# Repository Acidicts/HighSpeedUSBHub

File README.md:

# HighSpeedUSBHub

I looked at an old USB 2.0 hub I made and though what if I could make a faster one? So I did(whether it works or not is another story). This started right after I discovered the [texas instruments](https://www.ti.com/) site via the guide for making a flight controller by @notaroomba.

This is a USB 3.1 hub which uses a usb 3.1 gen 2 upstream port to 4 usb 3.0 downstream ports via a [`TUSB8041`](https://www.ti.com/product/TUSB8041). Each USB stack (I used x2 stacked usb 3.0 ports as they were more compact, and they reminded me of the raspberry pi 4) is powered by a [`TPS2051B`](https://www.ti.com/product/TPS2051B) which is a power switch that has a power limit of around 1A per controller as I recall.

### Features
- 4 USB-A 3.0 downstream ports
- 1 USB-C 3.1 gen 2 upstream port
- Powered by the USB-C port (5V 3A)
- Each downstream port is limited to 1A of current and with equal load across each port, 0.5A per port.
- CRYSTAL 24MHz clock for the TUSB8041

<div class="inline-flex">

</div>

### Case
Fusion 360 Link [here](https://a360.co/4czpJdL)
There are two parts of the case:
- The [Lid](case/Lid.stp)
- The [Base](case/Base.stp)
The lid has notches which slot into the base to hold it on using the power of friendship and friction.

### Getting Started
So ummm, how do I put this...

_*YOU PLUG IT IN*_

### Firmware
Sooo you won't believe this but it is just a usb hub, it is plug and play

### BOMs
- [BOM](BOM.csv)
- [PCB BOM](PCB_BOM.csv)

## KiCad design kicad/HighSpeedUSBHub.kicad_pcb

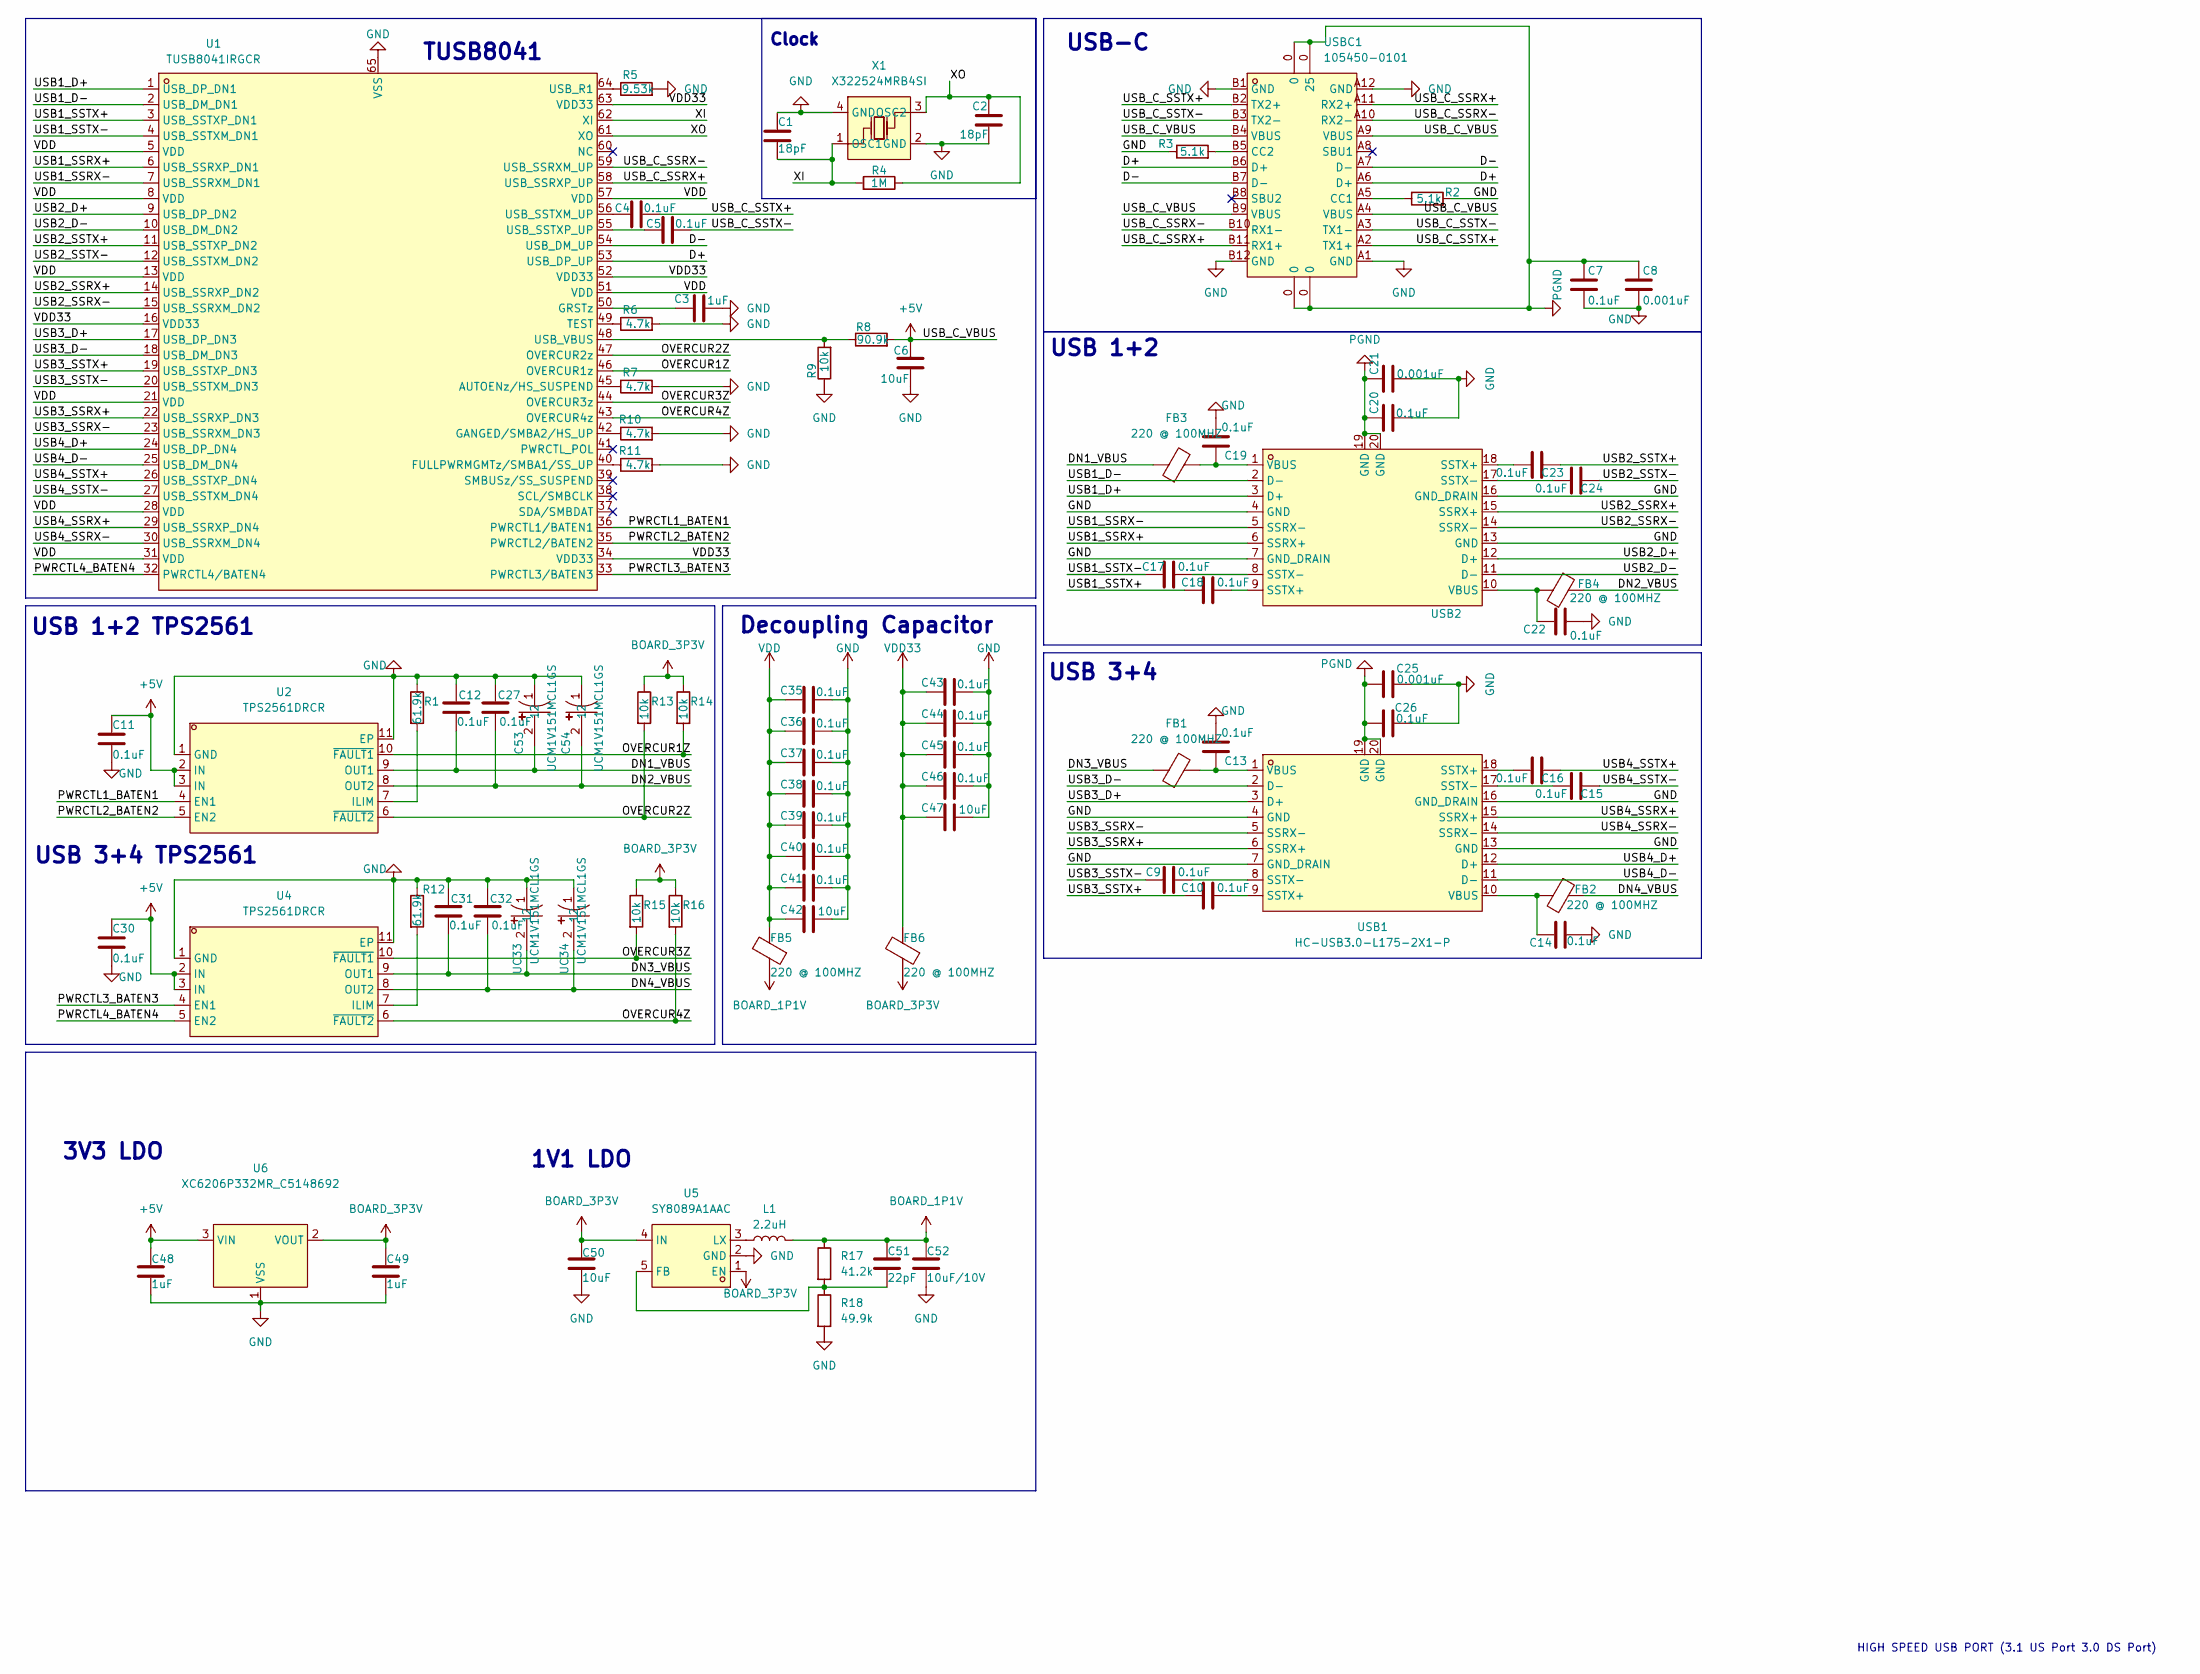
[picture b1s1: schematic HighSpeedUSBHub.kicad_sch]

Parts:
C1, C2: 18pF; C_0402_1005Metric
C3, C48, C49: 1uF; C_0603_1608Metric
C4, C5, C7, C9, C10, C11, C12, C13, C14, C15, C16, C17, C18, C19, C20, C22, C23, C24, C26, C27, C30, C31, C32, C35, C36, C37, C38, C39, C40, C41, C43, C44, C45, C46: 0.1uF; C_0402_1005Metric
C6: 10uF; C_0402_1005Metric
C8, C21, C25: 0.001uF; C_0402_1005Metric
C42, C47, C50: 10uF; C_0805_2012Metric
C51: 22pF; C_0402_1005Metric
C52: 10uF/10V; C_0402_1005Metric
C53, C54: UCM1V151MCL1GS; CAP-SMD_L6.6-W6.6; MPN UCM1V151MCL1GS; LCSC Part C729687
FB1, FB2, FB3, FB4, FB5, FB6: 220 @ 100MHZ; C_0402_1005Metric
L1: 2.2uH; L_Coilcraft_0403HQ_1008Metric
R1, R12: 61.9k; R_0805_2012Metric
R2, R3: 5.1k; R_0402_1005Metric
R4: 1M; R_0805_2012Metric
R5: 9.53k; R_0402_1005Metric
R6, R7, R10, R11: 4.7k; R_0402_1005Metric
R8: 90.9k; R_0402_1005Metric
R9, R13, R14, R15, R16: 10k; R_0402_1005Metric
R17: 41.2k; R_0402_1005Metric
R18: 49.9k; R_0603_1608Metric
U1: TUSB8041IRGCR; QFN-64_L9.0-W9.0-P0.50-BL-EP7.2; MPN TUSB8041IRGCR; LCSC Part C544686
U2, U4: TPS2561DRCR; VSON-10_L3.0-W3.0-P0.50-TL-EP_TPS62410DRCR; MPN TPS2561DRCR; LCSC Part C140303
U5: SY8089A1AAC; TSOT-23-5_L2.9-W1.6-P0.95-LS2.8-BR; MPN SY8089A1AAC; LCSC Part C479074
U6: XC6206P332MR_C5148692; SOT-23-3_L2.9-W1.3-P1.90-LS2.4-BR; MPN XC6206P332MR; LCSC Part C5148692
UC33, UC34: UCM1V151MCL1GS; CAP-SMD_L6.6-W6.6; MPN UCM1V151MCL1GS; LCSC Part C729687
USB1, USB2: HC-USB3.0-L175-2X1-P; USB-A-TH_H181-AF2R06-12ALCR; MPN HC-USB3.0-L175-2X1-P; LCSC Part C7501881
USBC1: 105450-0101; USB-C-SMD_TYPE-C-USB-18; MPN 1054500101; LCSC Part C134092
X1: X322524MRB4SI; CRYSTAL-SMD_4P-L3.2-W2.5-BL-2; MPN X322524MRB4SI; LCSC Part C70571

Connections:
+5V: C6.2, C11.1, C30.1, C48.1, R8.2, U2.2 (IN), U2.3 (IN), U4.2 (IN), U4.3 (IN), U6.3 (VIN), USBC1.A4 (VBUS), USBC1.A9 (VBUS), USBC1.B4 (VBUS), USBC1.B9 (VBUS)
/D+: U1.53 (USB_DP_UP), USBC1.A6 (D+), USBC1.B6 (D+)
/D-: U1.54 (USB_DM_UP), USBC1.A7 (D-), USBC1.B7 (D-)
/DN1_VBUS: C12.2, C53.2, FB3.1, U2.9 (OUT1)
/DN2_VBUS: C27.2, C54.2, FB4.1, U2.8 (OUT2)
/DN3_VBUS: C31.2, FB1.1, U4.9 (OUT1), UC33.2
/DN4_VBUS: C32.2, FB2.1, U4.8 (OUT2), UC34.2
/OVERCUR1Z: R14.2, U1.46 (OVERCUR1z), U2.10 (~FAULT1)
/OVERCUR2Z: R13.2, U1.47 (OVERCUR2z), U2.6 (~FAULT2)
/OVERCUR3Z: R15.2, U1.44 (OVERCUR3z), U4.10 (~FAULT1)
/OVERCUR4Z: R16.2, U1.43 (OVERCUR4z), U4.6 (~FAULT2)
/PWRCTL1_BATEN1: U1.36 (PWRCTL1/BATEN1), U2.4 (EN1)
/PWRCTL2_BATEN2: U1.35 (PWRCTL2/BATEN2), U2.5 (EN2)
/PWRCTL3_BATEN3: U1.33 (PWRCTL3/BATEN3), U4.4 (EN1)
/PWRCTL4_BATEN4: U1.32 (PWRCTL4/BATEN4), U4.5 (EN2)
/USB1_D+: U1.1 (USB_DP_DN1), USB2.3 (D+)
/USB1_D-: U1.2 (USB_DM_DN1), USB2.2 (D-)
/USB1_SSRX+: U1.6 (USB_SSRXP_DN1), USB2.6 (SSRX+)
/USB1_SSRX-: U1.7 (USB_SSRXM_DN1), USB2.5 (SSRX-)
/USB1_SSTX+: C18.1, U1.3 (USB_SSTXP_DN1)
/USB1_SSTX-: C17.1, U1.4 (USB_SSTXM_DN1)
/USB2_D+: U1.9 (USB_DP_DN2), USB2.12 (D+)
/USB2_D-: U1.10 (USB_DM_DN2), USB2.11 (D-)
/USB2_SSRX+: U1.14 (USB_SSRXP_DN2), USB2.15 (SSRX+)
/USB2_SSRX-: U1.15 (USB_SSRXM_DN2), USB2.14 (SSRX-)
/USB2_SSTX+: C23.1, U1.11 (USB_SSTXP_DN2)
/USB2_SSTX-: C24.1, U1.12 (USB_SSTXM_DN2)
/USB3_D+: U1.17 (USB_DP_DN3), USB1.3 (D+)
/USB3_D-: U1.18 (USB_DM_DN3), USB1.2 (D-)
/USB3_SSRX+: U1.22 (USB_SSRXP_DN3), USB1.6 (SSRX+)
/USB3_SSRX-: U1.23 (USB_SSRXM_DN3), USB1.5 (SSRX-)
/USB3_SSTX+: C10.1, U1.19 (USB_SSTXP_DN3)
/USB3_SSTX-: C9.1, U1.20 (USB_SSTXM_DN3)
/USB4_D+: U1.24 (USB_DP_DN4), USB1.12 (D+)
/USB4_D-: U1.25 (USB_DM_DN4), USB1.11 (D-)
/USB4_SSRX+: U1.29 (USB_SSRXP_DN4), USB1.15 (SSRX+)
/USB4_SSRX-: U1.30 (USB_SSRXM_DN4), USB1.14 (SSRX-)
/USB4_SSTX+: C16.1, U1.26 (USB_SSTXP_DN4)
/USB4_SSTX-: C15.1, U1.27 (USB_SSTXM_DN4)
/USB_C_SSRX+: U1.58 (USB_SSRXP_UP), USBC1.A11 (RX2+), USBC1.B11 (RX1+)
/USB_C_SSRX-: U1.59 (USB_SSRXM_UP), USBC1.A10 (RX2-), USBC1.B10 (RX1-)
/USB_C_SSTX+: C4.2, USBC1.A2 (TX1+), USBC1.B2 (TX2+)
/USB_C_SSTX-: C5.2, USBC1.A3 (TX1-), USBC1.B3 (TX2-)
/XI: C1.2, R4.2, U1.62 (XI), X1.1 (OSC1)
/XO: C2.1, R4.1, U1.61 (XO), X1.3 (OSC2)
BOARD_1P1V: C51.1, C52.1, FB5.1, L1.2, R17.1
BOARD_3P3V: C49.1, C50.1, FB6.1, R13.1, R14.1, R15.1, R16.1, U5.1 (EN), U5.4 (IN), U6.2 (VOUT)
GND: C1.1, C2.2, C3.2, C6.1, C7.2, C8.2, C11.2, C12.1, C13.2, C14.2, C19.2, C20.2, C21.2, C22.2, C25.2, C26.2, C27.1, C30.2, C31.1, C32.1, C35.2, C36.2, C37.2, C38.2, C39.2, C40.2, C41.2, C42.2, C43.2, C44.2, C45.2, C46.2, C47.2, C48.2, C49.2, C50.2, C52.2, C53.1, C54.1, R1.1, R2.2, R3.1, R5.2, R6.2, R7.2, R9.1, R10.2, R11.2, R12.1, R18.2, U1.65 (VSS), U2.1 (GND), U2.11 (EP), U4.1 (GND), U4.11 (EP), U5.2 (GND), U6.1 (VSS), UC33.1, UC34.1, USB1.4 (GND), USB1.7 (GND_DRAIN), USB1.13 (GND), USB1.16 (GND_DRAIN), USB2.4 (GND), USB2.7 (GND_DRAIN), USB2.13 (GND), USB2.16 (GND_DRAIN), USBC1.A1 (GND), USBC1.A12 (GND), USBC1.B1 (GND), USBC1.B12 (GND), X1.2 (GND), X1.4 (GND)
unnamed: C9.2, USB1.8 (SSTX-)
unnamed: C10.2, USB1.9 (SSTX+)
unnamed: C13.1, FB1.2, USB1.1 (VBUS)
unnamed: C14.1, FB2.2, USB1.10 (VBUS)
unnamed: C15.2, USB1.17 (SSTX-)
unnamed: C16.2, USB1.18 (SSTX+)
unnamed: C17.2, USB2.8 (SSTX-)
unnamed: C18.2, USB2.9 (SSTX+)
unnamed: C19.1, FB3.2, USB2.1 (VBUS)
unnamed: C22.1, FB4.2, USB2.10 (VBUS)
unnamed: C23.2, USB2.18 (SSTX+)
unnamed: C24.2, USB2.17 (SSTX-)
unnamed: R7.1, U1.45 (AUTOENz/HS_SUSPEND)
unnamed: R11.1, U1.40 (FULLPWRMGMTz/SMBA1/SS_UP)
unnamed: R10.1, U1.42 (GANGED/SMBA2/HS_UP)
unnamed: C3.1, U1.50 (GRSTz)
unnamed: R6.1, U1.49 (TEST)
unnamed: R5.1, U1.64 (USB_R1)
unnamed: C4.1, U1.56 (USB_SSTXM_UP)
unnamed: C5.1, U1.55 (USB_SSTXP_UP)
unnamed: R8.1, R9.2, U1.48 (USB_VBUS)
unnamed: R1.2, U2.7 (ILIM)
unnamed: R12.2, U4.7 (ILIM)
unnamed: C51.2, R17.2, R18.1, U5.5 (FB)
unnamed: L1.1, U5.3 (LX)
unnamed: R2.1, USBC1.A5 (CC1)
unnamed: R3.2, USBC1.B5 (CC2)
PGND: C7.1, C8.1, C20.1, C21.1, C25.1, C26.1, USB1.19 (GND), USB1.20 (GND), USB2.19 (GND), USB2.20 (GND), USBC1.0
VDD: C35.1, C36.1, C37.1, C38.1, C39.1, C40.1, C41.1, C42.1, FB5.2, U1.5 (VDD), U1.8 (VDD), U1.13 (VDD), U1.21 (VDD), U1.28 (VDD), U1.31 (VDD), U1.51 (VDD), U1.57 (VDD)
VDD33: C43.1, C44.1, C45.1, C46.1, C47.1, FB6.2, U1.16 (VDD33), U1.34 (VDD33), U1.52 (VDD33), U1.63 (VDD33)

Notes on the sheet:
3V3 LDO
TUSB8041
USB 1+2 TPS2561
USB 3+4 TPS2561
1V1 LDO
USB 1+2
USB 3+4
Clock
Decoupling Capacitor
USB-C
HIGH SPEED USB PORT (3.1 US Port 3.0 DS Port)

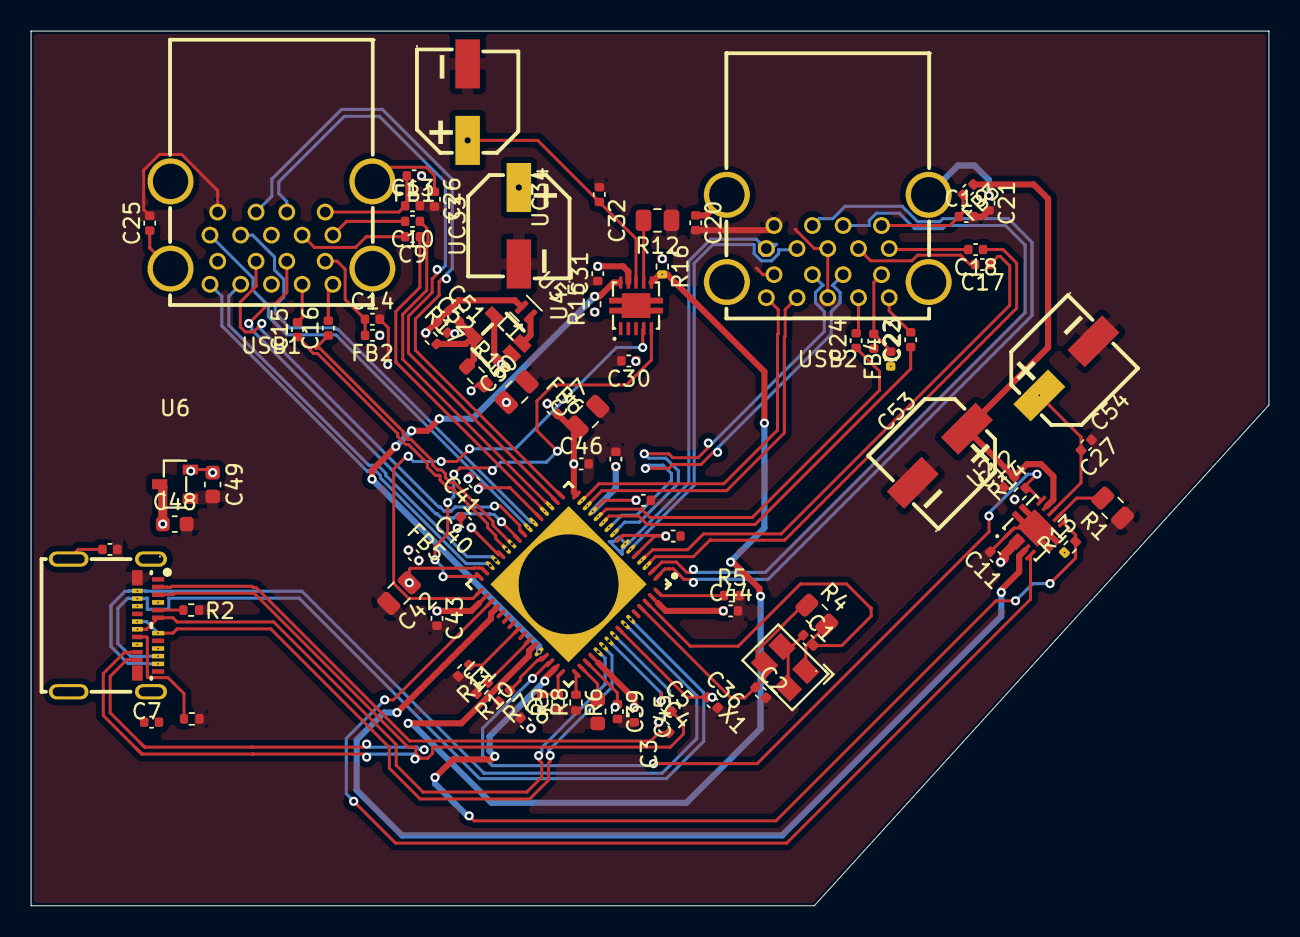
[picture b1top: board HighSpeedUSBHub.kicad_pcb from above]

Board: 4 copper layers, 80.6 x 57.0 mm, 86 parts (0 on the bottom side), 78 nets.

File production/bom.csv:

Designator,Footprint,Quantity,Value,LCSC Part #
"C1, C2",0402,2,18pF,
"C10, C11, C12, C13, C14, C15, C16, C17, C18, C19, C20, C22, C23, C24, C26, C27, C30, C31, C32, C35, C36, C37, C38, C39, C4, C40, C41, C43, C44, C45, C46, C5, C7, C9",0402,34,0.1uF,
"C21, C25, C8",0402,3,0.001uF,
"C3, C48, C49",0603,3,1uF,
"C42, C47, C50",0805,3,10uF,
C51,0402,1,22pF,
C52,0402,1,10uF/10V,
"C53, C54, UC33, UC34",CAP-SMD_L6.6-W6.6,4,UCM1V151MCL1GS,C729687
C6,0402,1,10uF,
"FB1, FB2, FB3, FB4, FB5, FB6",0402,6,220 @ 100MHZ,
L1,L_Coilcraft_0403HQ_1008Metric,1,2.2uH,
"R1, R12",0805,2,61.9k,
"R10, R11, R6, R7",0402,4,4.7k,
"R13, R14, R15, R16, R9",0402,5,10k,
R17,0402,1,41.2k,
R18,0603,1,49.9k,
"R2, R3",0402,2,5.1k,
R4,0805,1,1M,
R5,0402,1,9.53k,
R8,0402,1,90.9k,
U1,QFN-64_L9.0-W9.0-P0.50-BL-EP7.2,1,TUSB8041IRGCR,C544686
"U2, U4",VSON-10_L3.0-W3.0-P0.50-TL-EP_TPS62410DRCR,2,TPS2561DRCR,C140303
U5,TSOT-23-5_L2.9-W1.6-P0.95-LS2.8-BR,1,SY8089A1AAC,C479074
U6,SOT-23-3_L2.9-W1.3-P1.90-LS2.4-BR,1,XC6206P332MR_C5148692,C5148692
"USB1, USB2",USB-A-TH_H181-AF2R06-12ALCR,2,HC-USB3.0-L175-2X1-P,C7501881
USBC1,USB-C-SMD_TYPE-C-USB-18,1,105450-0101,C134092
X1,CRYSTAL-SMD_4P-L3.2-W2.5-BL-2,1,X322524MRB4SI,C70571
